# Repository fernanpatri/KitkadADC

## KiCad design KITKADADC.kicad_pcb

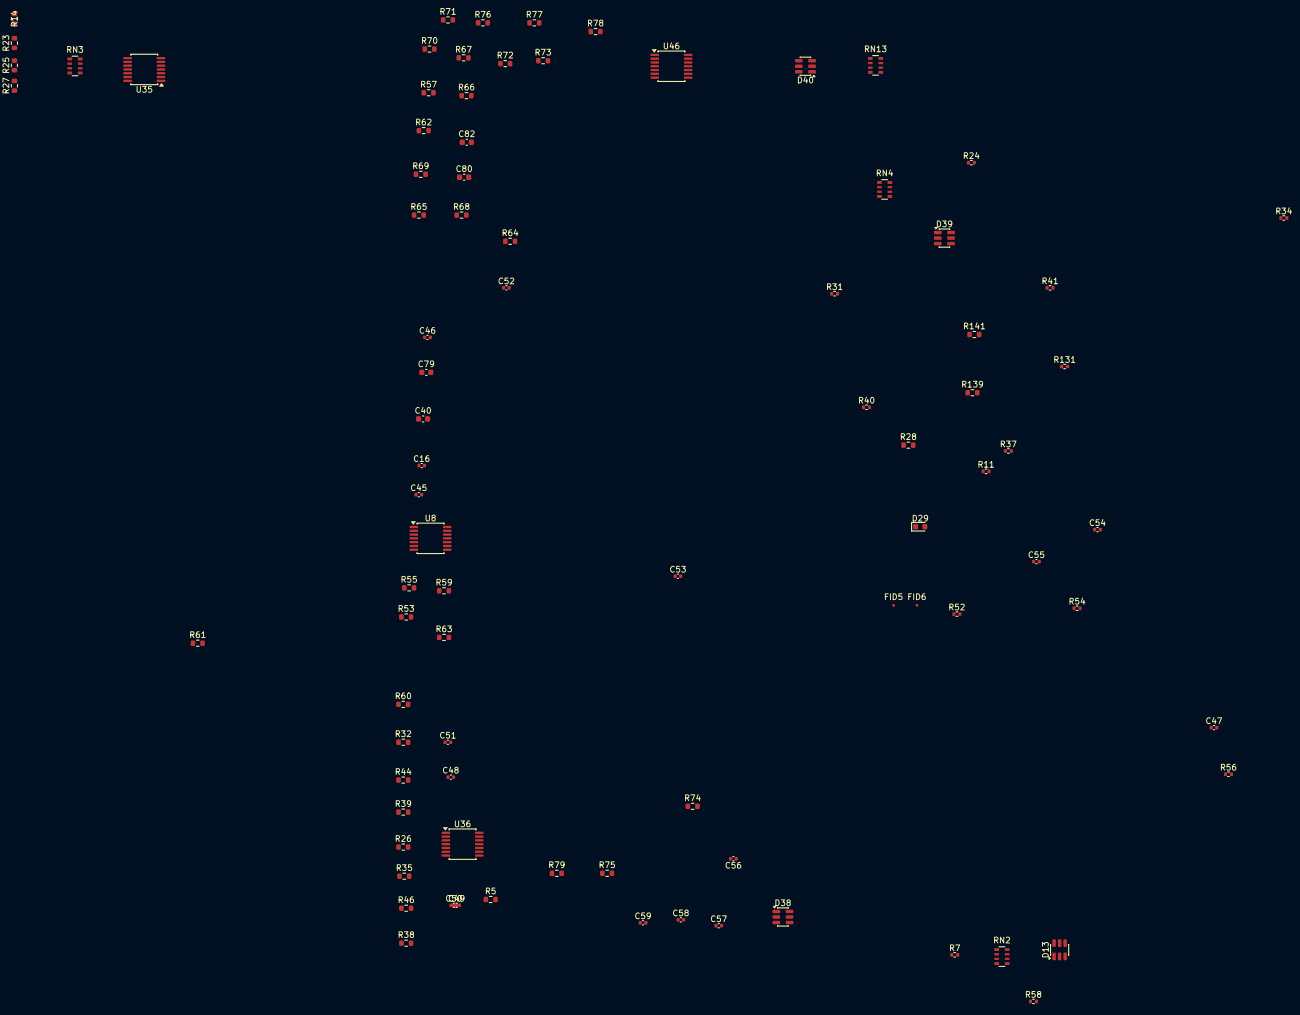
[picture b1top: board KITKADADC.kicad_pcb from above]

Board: 2 copper layers, 87 parts (0 on the bottom side), 68 nets, no tracks yet.

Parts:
C16, C45, C46, C47, C48, C49, C50, C51, C52, C53, C54, C55, C56, C57, C58, C59: 100nF; C_0402_1005Metric
C40, C79, C80, C82: 10nF; C_0603_1608Metric
D13, D38, D39, D40: SRV05-4; SOT-23-6
D29: LED-RED; LED_0603_1608Metric
FID5, FID6: Fiducial; Fiducial_0.5mm_Mask1mm
R5, R26, R32, R35, R53, R55, R57, R59, R64, R65, R66, R67, R72, R73, R74, R75: 6.8K; R_0603_1608Metric
R7, R11, R40: DNP; R_0402_1005Metric
R14, R23, R25, R27: 2.7k; R_0603_1608Metric
R24, R31, R34, R37, R41, R52, R54, R56, R58, R131: 470K; R_0402_1005Metric
R28: 2.2k; R_0603_1608Metric
R38, R39, R44, R46, R60, R61, R62, R63, R68, R69, R70, R71, R76, R77, R78, R79, R141: 10K; R_0603_1608Metric
R139: 39k; R_0603_1608Metric
RN2, RN3, RN4, RN13: 10k; R_Array_Convex_4x0603
U8, U35, U36, U46: MCP6004; TSSOP-14_4.4x5mm_P0.65mm

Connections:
/5V: C40.1, C79.1, C80.1, C82.1, D13.5, D29.2 (A), D38.5, D39.5, D40.5, R7.1, R11.2, R14.2, R23.2, R25.2, R27.2, R40.2, U8.4 (V+), U35.4 (V+), U36.4 (V+), U46.4 (V+)
/AGND: R38.1, R39.1, R44.1, R46.1, R60.1, R61.1, R62.1, R63.1, R68.1, R69.1, R70.1, R71.1, R76.1, R77.1, R78.1, R79.1
/AT1: R27.1, RN3.4 (R4.1)
/AT1_MCU: R67.1, R71.2
/AT2: R25.1, RN3.3 (R3.1)
/AT2_MCU: R66.1, R70.2
/AT3: R23.1, RN3.2 (R2.1)
/AT3_MCU: R65.1, R69.2
/AT4: R14.1, RN3.1 (R1.1)
/AT4_MCU: R64.1, R68.2
/AV1: R37.1, RN4.4 (R4.1)
/AV1_MCU: R35.1, R46.2
/AV2: R31.1, RN4.2 (R2.1)
/AV2_MCU: R26.1, R39.2
/AV3: R24.1, RN4.1 (R1.1)
/AV3_MCU: R5.1, R38.2
/AV4: R11.1, R131.1, RN13.2 (R2.1)
/AV4_MCU: R73.1, R77.2
/AV5: R40.1, R41.1, RN13.1 (R1.1)
/AV5_MCU: R72.1, R76.2
/AV6: R58.1, RN2.4 (R4.1)
/AV6_MCU: R59.1, R63.2
/AV7: R56.1, RN2.3 (R3.1)
/AV7_MCU: R57.1, R62.2
/AV8: R54.1, RN2.2 (R2.1)
/AV8_MCU: R55.1, R61.2
/AV9: R7.2, R52.1, RN2.1 (R1.1)
/AV9_MCU: R53.1, R60.2
/AV10: R34.1, RN4.3 (R3.1)
/AV10_MCU: R32.1, R44.2
/AV11_MCU: R75.1, R79.2
/CAM: R28.1, RN13.4 (R4.1)
/CAM_MCU: C59.1, D40.4, RN13.5 (R4.2), U46.3 (+)
/Vbat_MCU: R74.1, R78.2
GND: C16.2, C40.2, C45.2, C46.2, C47.2, C48.2, C49.2, C50.2, C51.2, C52.2, C53.2, C54.2, C55.2, C56.2, C57.2, C58.2, C59.2, C79.2, C80.2, C82.2, D13.2, D38.2, D39.2, D40.2, R24.2, R31.2, R34.2, R37.2, R41.2, R52.2, R54.2, R56.2, R58.2, R131.2, R141.2, U8.11 (V-), U35.11 (V-), U36.11 (V-), U46.11 (V-)
unnamed: D29.1 (K), R28.2
unnamed: C16.1, D13.6, RN2.8 (R1.2), U8.5 (+)
unnamed: C45.1, D13.4, RN2.7 (R2.2), U8.3 (+)
unnamed: C46.1, D13.3, RN2.6 (R3.2), U8.12 (+)
unnamed: C47.1, D13.1, RN2.5 (R4.2), U8.10 (+)
unnamed: C52.1, D38.6, RN3.8 (R1.2), U35.5 (+)
unnamed: C53.1, D38.4, RN3.7 (R2.2), U35.3 (+)
unnamed: C54.1, D38.3, RN3.6 (R3.2), U35.12 (+)
unnamed: C55.1, D38.1, RN3.5 (R4.2), U35.10 (+)
unnamed: C48.1, D39.3, RN4.8 (R1.2), U36.12 (+)
unnamed: C49.1, D39.1, RN4.7 (R2.2), U36.10 (+)
unnamed: C50.1, D39.6, RN4.6 (R3.2), U36.5 (+)
unnamed: C51.1, D39.4, RN4.5 (R4.2), U36.3 (+)
unnamed: C56.1, D40.3, RN13.8 (R1.2), U46.12 (+)
unnamed: C57.1, D40.1, RN13.7 (R2.2), U46.10 (+)
unnamed: R139.1, R141.1, RN13.3 (R3.1)
unnamed: C58.1, D40.6, RN13.6 (R3.2), U46.5 (+)
unnamed: R55.2, U8.1, U8.2 (-)
unnamed: R53.2, U8.6 (-), U8.7
unnamed: R59.2, U8.8, U8.9 (-)
unnamed: R57.2, U8.13 (-), U8.14
unnamed: R65.2, U35.1, U35.2 (-)
unnamed: R64.2, U35.6 (-), U35.7
unnamed: R67.2, U35.8, U35.9 (-)
unnamed: R66.2, U35.13 (-), U35.14
unnamed: R35.2, U36.1, U36.2 (-)
unnamed: R32.2, U36.6 (-), U36.7
unnamed: R26.2, U36.8, U36.9 (-)
unnamed: R5.2, U36.13 (-), U36.14
unnamed: R75.2, U46.1, U46.2 (-)
unnamed: R74.2, U46.6 (-), U46.7
unnamed: R73.2, U46.8, U46.9 (-)
unnamed: R72.2, U46.13 (-), U46.14

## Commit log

2026-04-27 primera repositoriokitkad
2026-04-30 he puesto un diodo
2026-05-01 empezando con el adc
2026-05-01 ordenando PCB
2026-05-01 ordenando
2026-05-02 recolocando pcb
